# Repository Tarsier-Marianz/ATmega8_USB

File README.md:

# ATmega8-USB

A simple USB based prototyping board for Atmel's AVR microcontrollers (ATmega8).

### Thanks

[KiCad IDE](http://kicad-pcb.org/) - for letting me use a free software in designing PCB

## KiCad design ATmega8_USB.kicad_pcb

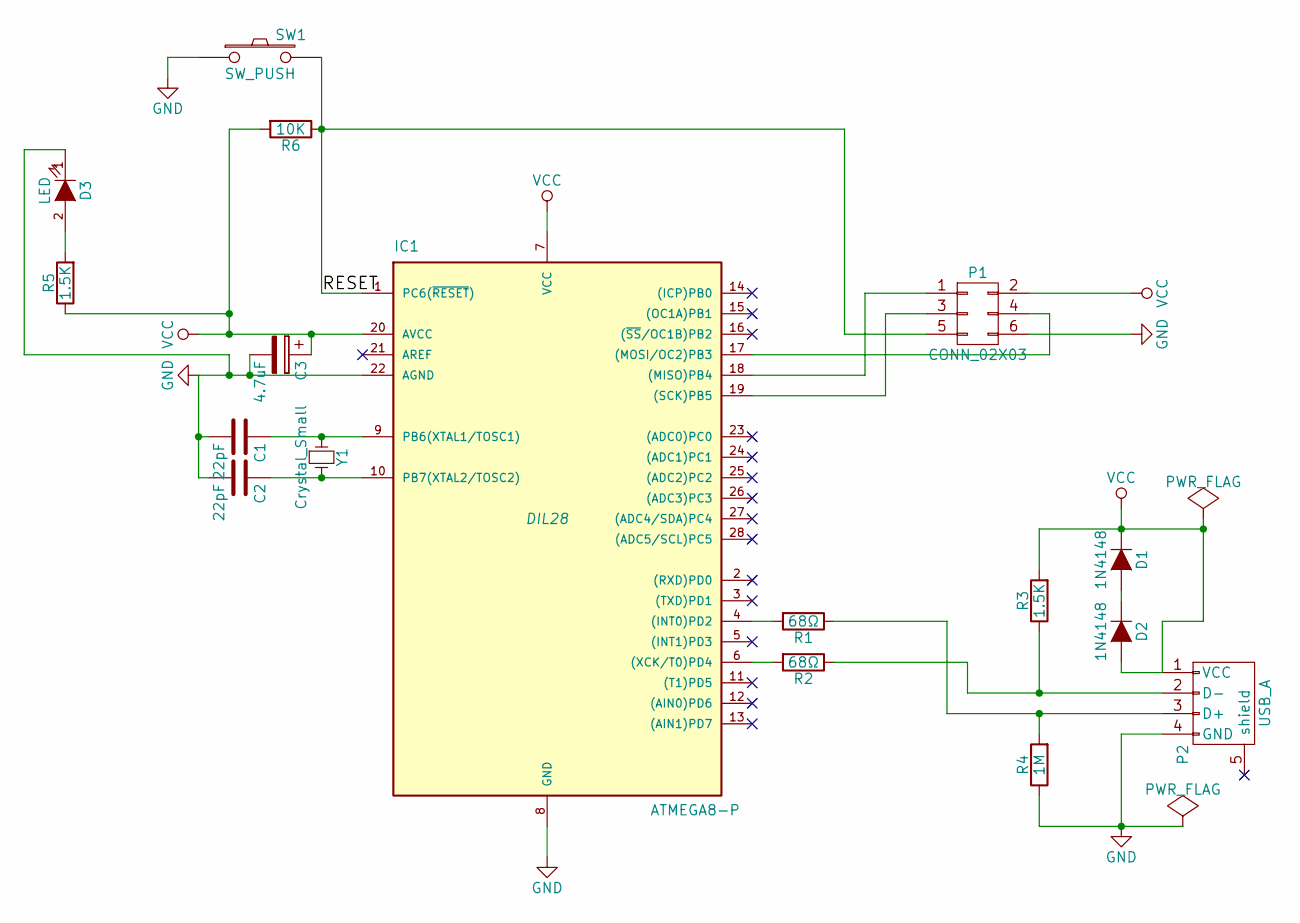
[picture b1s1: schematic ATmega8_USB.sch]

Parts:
C1, C2: 22pF; C_Disc_D5.0mm_W2.5mm_P2.50mm
C3: 4.7uF; CP_Radial_D5.0mm_P2.50mm
D1, D2: 1N4148; D_DO-41_SOD81_P7.62mm_Horizontal
D3: LED; LED_D3.0mm
IC1: ATMEGA8-P; DIL28
P1: CONN_02X03; Pin_Header_Straight_2x03_Pitch2.54mm
P2: USB_A
R1, R2: 68Ω; R_Axial_DIN0204_L3.6mm_D1.6mm_P7.62mm_Horizontal
R3, R5: 1.5K; R_Axial_DIN0204_L3.6mm_D1.6mm_P7.62mm_Horizontal
R4: 1M; R_Axial_DIN0204_L3.6mm_D1.6mm_P7.62mm_Horizontal
R6: 10K; R_Axial_DIN0204_L3.6mm_D1.6mm_P7.62mm_Horizontal
SW1: SW_PUSH; SW_PUSH_6mm_h5mm
Y1: Crystal_Small; Resonator-2pin_w10.0mm_h5.0mm

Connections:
/RESET: IC1.1 (PC6(~RESET~)), P1.5, R6.1, SW1.2
GND: C1.2, C2.2, C3.2, D3.1 (K), IC1.8 (GND), IC1.22 (AGND), P1.6, P2.4 (GND), R4.1, SW1.1
unnamed: C1.1, IC1.9 (PB6(XTAL1/TOSC1)), Y1.1
unnamed: C2.1, IC1.10 (PB7(XTAL2/TOSC2)), Y1.2
unnamed: D1.2 (A), D2.1 (K)
unnamed: D3.2 (A), R5.2
unnamed: IC1.4 ((INT0)PD2), R1.2
unnamed: IC1.6 ((XCK/T0)PD4), R2.2
unnamed: IC1.17 ((MOSI/OC2)PB3), P1.4
unnamed: IC1.18 ((MISO)PB4), P1.1
unnamed: IC1.19 ((SCK)PB5), P1.3
unnamed: P2.2 (D-), R2.1, R3.1
unnamed: P2.3 (D+), R1.1, R4.2
VCC: C3.1, D1.1 (K), D2.2 (A), IC1.7 (VCC), IC1.20 (AVCC), P1.2, P2.1 (VCC), R3.2, R5.1, R6.2

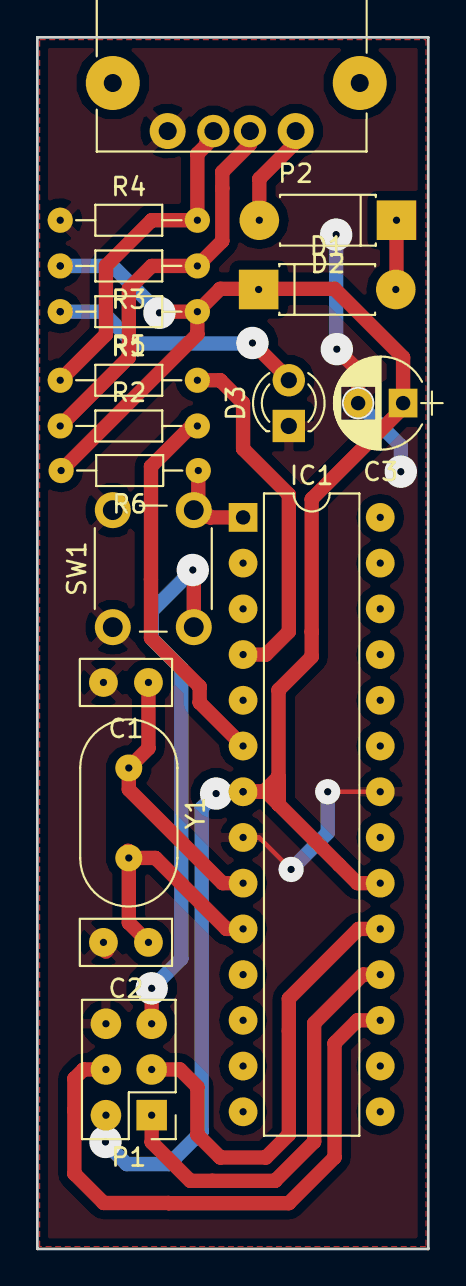
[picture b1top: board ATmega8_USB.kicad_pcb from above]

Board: 2 copper layers, 21.7 x 67.3 mm, 17 parts (0 on the bottom side), 14 nets.

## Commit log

2018-02-27 Add readme details
2018-02-27 Fixed readme link
